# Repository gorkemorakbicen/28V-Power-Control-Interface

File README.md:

# 28 V Power Control Interface

Four-layer PCB design for a nominal 28 V DC input, with input protection, a 5 V buck converter, a 3.3 V logic supply, STM32 voltage-sensing inputs, and a CAN physical interface.

> **Project status:** Schematic capture and PCB layout are complete. The design report records zero KiCad ERC/DRC errors. **No PCB has been fabricated, no firmware is included, and no electrical or EMC measurements have been performed.** All calculated operating values below are design estimates, not test results.

## Overview

This personal hardware-design project explores the process of developing a compact monitoring and communication board for a nominal 28 V DC supply. The work covers component selection, hand calculations, schematic capture, four-layer PCB layout, basic design-rule verification, and technical documentation.

The board is *not* an experimentally validated power supply or a product qualified for automotive, aviation, or industrial transient/EMC standards.

## Key specifications

| Item | Design value / implementation |
| --- | --- |
| Nominal input | 28 V DC |
| Input protection | 1 A fuse, SMBJ36CA bidirectional TVS, P-channel MOSFET reverse-polarity stage, gate Zener |
| Main converter | Texas Instruments LM5164 synchronous buck |
| Buck output | Approximately 5 V; **1 A design target** (not measured) |
| Approximate switching frequency | 303 kHz, calculated from the selected RON resistor |
| Power inductor | 47 µH, Coilcraft MSS1260T-473MLD |
| Logic supply | 3.3 V, TLV75533 LDO |
| Microcontroller | STM32G0B1CBT6, 16 MHz external crystal |
| Voltage-sensing inputs | Resistor-divider/RC-filter networks for nominal 5 V and 28 V rails, connected to STM32 ADC pins |
| CAN interface | NXP TJA1049 transceiver, CAN-line ESD protection, optional 120 Ω termination (DNP) |
| Programming interface | 5-pin SWD header and reset pushbutton |
| PCB size | 70.25 × 67.75 mm |
| PCB stack-up | F.Cu / In1.Cu (GND) / In2.Cu (GND) / B.Cu; nominal 1.6 mm board thickness |
| EDA tool | KiCad 10.0 |

## System architecture

```mermaid
flowchart TD
    A["28 V DC input"] --> B["Fuse, TVS and PMOS protection"]
    B --> C["LM5164 buck: 5 V"]
    C --> D["TLV75533 LDO: 3.3 V"]
    D --> E["STM32G0B1 controller"]
    C --> F["TJA1049 CAN transceiver"]
    E <--> F
    B --> G["28 V sensing divider"]
    C --> H["5 V sensing divider"]
    G --> E
    H --> E
```

The STM32 hardware provides ADC connections for rail monitoring and digital connections to the CAN transceiver. Firmware for sampling, calibration, reporting, and CAN communication remains future work.

## Design highlights

### 1. Input protection

- A 1 A fuse is provided for sustained overcurrent protection.
- An SMBJ36CA TVS is used for transient suppression; its standoff and clamping characteristics must be assessed against a defined source and transient profile.
- A P-channel MOSFET provides reverse-polarity protection. A 12 V Zener network limits the magnitude of its gate-to-source voltage.
- Protection coordination and survival under specified surge waveforms have **not** been verified by test.

### 2. Buck converter and component sizing

- The LM5164 stage converts a nominal 28 V input into an approximately 5 V rail.
- The selected 316 kΩ / 100 kΩ feedback divider gives a nominal calculated output of approximately **4.992 V**.
- The chosen 47 µH inductor and approximately 303 kHz switching frequency yield a calculated inductor-current ripple of **0.288 A** at the nominal design point.
- A 22 µF output capacitor is populated; the second 22 µF position (C7) is marked **DNP**.
- PCB placement emphasizes the switching-current loop, a restrained SW-node area, and feedback routing away from noisy nodes.

### 3. Monitoring, programming, and CAN

- The 5 V measurement divider scales a nominal 5 V input to approximately **2.500 V** at the ADC input.
- The 28 V measurement divider scales a nominal 28 V input to approximately **0.824 V**.
- Both measurement paths include RC filtering. Appropriate ADC sampling time and calibration would need to be addressed in firmware.
- The CAN physical interface uses a TJA1049 transceiver and an ESD suppressor. A 120 Ω termination position (R15) is provided but not populated by default; termination depends on the node's position in the CAN network.

### 4. Four-layer PCB

The two internal copper layers are assigned to GND fills to support return-current paths for top- and bottom-layer routing. Component placement considers the buck power loop, local MCU decoupling, crystal proximity, and CAN protection near the external connector.

See the [four-page PCB layer exports](docs/PCB_Layer_Exports.pdf), a [color top-layer view](docs/PCB_Top_Layer_View.pdf), and the [complete schematic](docs/Complete_Schematic.pdf).

## Verification and limitations

| Activity | Status |
| --- | --- |
| Component selection and hand calculations | Documented |
| Schematic capture and PCB layout | Complete |
| KiCad ERC / DRC | **0 errors recorded in the design report**; not independently rerun for this publication |
| Physical PCB fabrication and assembly | Not performed |
| Power-up, oscilloscope, thermal, and CAN tests | Not performed |
| Embedded firmware and closed-loop control | Not included |
| Defined transient/EMC standard compliance | Not designed or verified |

The layout's passing design-rule checks do not establish electrical performance, manufacturability, or standards compliance. In particular, transient protection, thermal behavior, regulator stability, and sensing accuracy require further review and practical validation.

## Repository contents

```text
28V-Power-Control-Interface/
├── README.md
├── hardware/
│   ├── 28V_Power_Control_Interface.kicad_pro
│   ├── 28V_Power_Control_Interface.kicad_sch
│   ├── MCU_CAN.kicad_sch
│   └── 28V_Power_Control_Interface.kicad_pcb
├── docs/
│   ├── Technical_Design_Report_TR.pdf
│   ├── Complete_Schematic.pdf
│   ├── PCB_Layer_Exports.pdf
│   ├── PCB_Top_Layer_View.pdf
│   └── BOM.xlsx
└── images/
    └── PCB_3D.png
```

### Open the design

1. Install a compatible version of **KiCad 10**.
2. Open `hardware/28V_Power_Control_Interface.kicad_pro`.
3. Keep the top-level schematic and `MCU_CAN.kicad_sch` in the same directory so the hierarchical sheet resolves correctly.

### Documentation

- [Technical design report (Turkish, 18 pages)](docs/Technical_Design_Report_TR.pdf) — design rationale, calculations, electrical assumptions, PCB decisions, and limitations.
- [Complete schematic (PDF)](docs/Complete_Schematic.pdf)
- [PCB layer exports (four-page PDF)](docs/PCB_Layer_Exports.pdf)
- [Color top-layer view (PDF)](docs/PCB_Top_Layer_View.pdf)
- [Bill of materials (Excel)](docs/BOM.xlsx) — includes part numbers and DNP information.

## Author

**Görkem Orakbiçen**  
Electrical and Electronics Engineering, Dokuz Eylül University

This is an independently developed portfolio design. It does not represent a validated or production-released hardware product.

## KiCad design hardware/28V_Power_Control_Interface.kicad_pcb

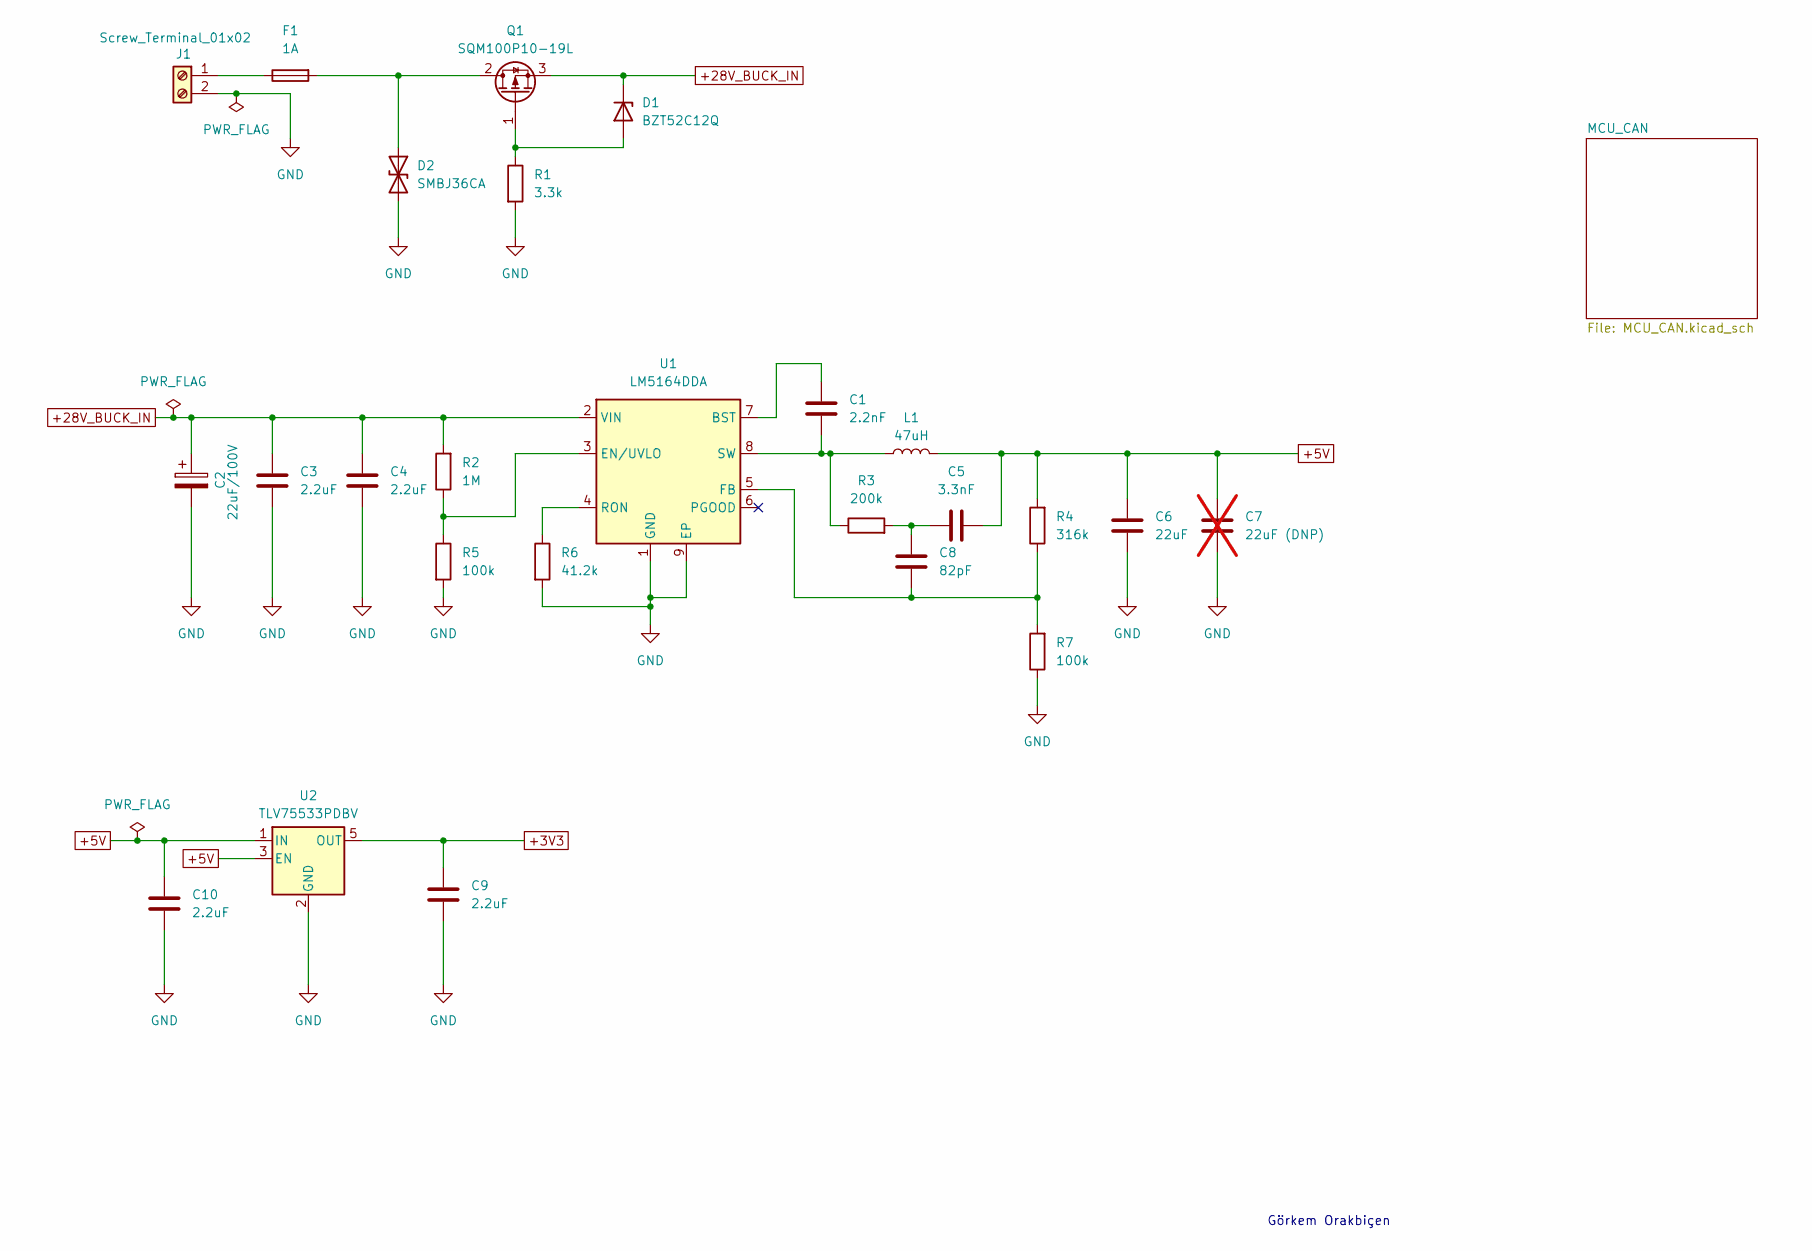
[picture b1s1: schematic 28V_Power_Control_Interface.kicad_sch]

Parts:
C1: 2.2nF; C_0402_1005Metric; MPN GCM155R71H222KA37D
C2: 22uF/100V; CP_Elec_10x10; MPN UCZ2A220MCS1GS
C3, C4: 2.2uF; C_1210_3225Metric; MPN CGA6N3X7R2A225K230AB
C5: 3.3nF; C_0603_1608Metric; MPN GRM188R72A332KA01D
C6: 22uF; C_1210_3225Metric; MPN CGA6P1X7R1C226M250AC
C7: 22uF (DNP); C_1210_3225Metric; MPN CGA6P1X7R1C226M250AC; not fitted
C8: 82pF; C_0603_1608Metric; MPN CGA3E2C0G1H820J080AA
C9, C10: 2.2uF; C_0805_2012Metric; MPN GRM21BR71C225KA12L
D1: BZT52C12Q; D_SOD-123; MPN BZT52C12Q-7-F
D2: SMBJ36CA; D_SMB; MPN SMBJ36CA
F1: 1A; Fuse_Littelfuse-NANO2-451_453; MPN 0451001.MRL
J1: Screw_Terminal_01x02; TerminalBlock_Phoenix_MKDS-1,5-2-5.08_1x02_P5.08mm_Horizont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; MPN 1715721
L1: 47uH; L_Coilcraft_MSS1260-XXX; MPN MSS1260T-473MLD
Q1: SQM100P10-19L; TO-263-3_TabPin2; MPN SQM100P10-19L_GE3
R1: 3.3k; R_1206_3216Metric; MPN AC1206FR-073K3L
R2: 1M; R_0603_1608Metric; MPN AC0603FR-071ML
R3: 200k; R_0603_1608Metric; MPN AC0603FR-07200KL
R4: 316k; R_0603_1608Metric; MPN RT0603BRD07316KL
R5: 100k; R_0603_1608Metric; MPN AC0603FR-07100KL
R6: 41.2k; R_0603_1608Metric; MPN AC0603FR-0741K2L
R7: 100k; R_0603_1608Metric; MPN RT0603BRD07100KL
U1: LM5164DDA; HSOP-8-1EP_3.9x4.9mm_P1.27mm_EP2.41x3.1mm_ThermalVias; MPN LM5164DDAT
U2: TLV75533PDBV; SOT-23-5; MPN TLV75533PDBVR

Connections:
+3V3: C9.1, U2.5 (OUT); also elsewhere on the board
+5V: C5.1, C6.2, C7.2, C10.1, L1.2, R4.2, U2.1 (IN), U2.3 (EN); also elsewhere on the board
+28V_BUCK_IN: C2.1, C3.2, C4.2, D1.1 (K), Q1.3 (S), R2.2, U1.2 (VIN); also elsewhere on the board
GND: C2.2, C3.1, C4.1, C6.1, C7.1, C9.2, C10.2, D2.2 (A2), J1.2, R1.2, R5.2, R6.2, R7.1, U1.1 (GND), U1.9 (EP), U2.2 (GND); also elsewhere on the board
unnamed: C5.2, C8.2, R3.2
unnamed: D1.2 (A), Q1.1 (G), R1.1
unnamed: D2.1 (A1), F1.2, Q1.2 (D)
unnamed: F1.1, J1.1
unnamed: C1.2, U1.7 (BST)
unnamed: R2.1, R5.1, U1.3 (EN/UVLO)
unnamed: C8.1, R4.1, R7.2, U1.5 (FB)
unnamed: R6.1, U1.4 (RON)
unnamed: C1.1, L1.1, R3.1, U1.8 (SW)

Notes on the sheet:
Görkem Orakbiçen

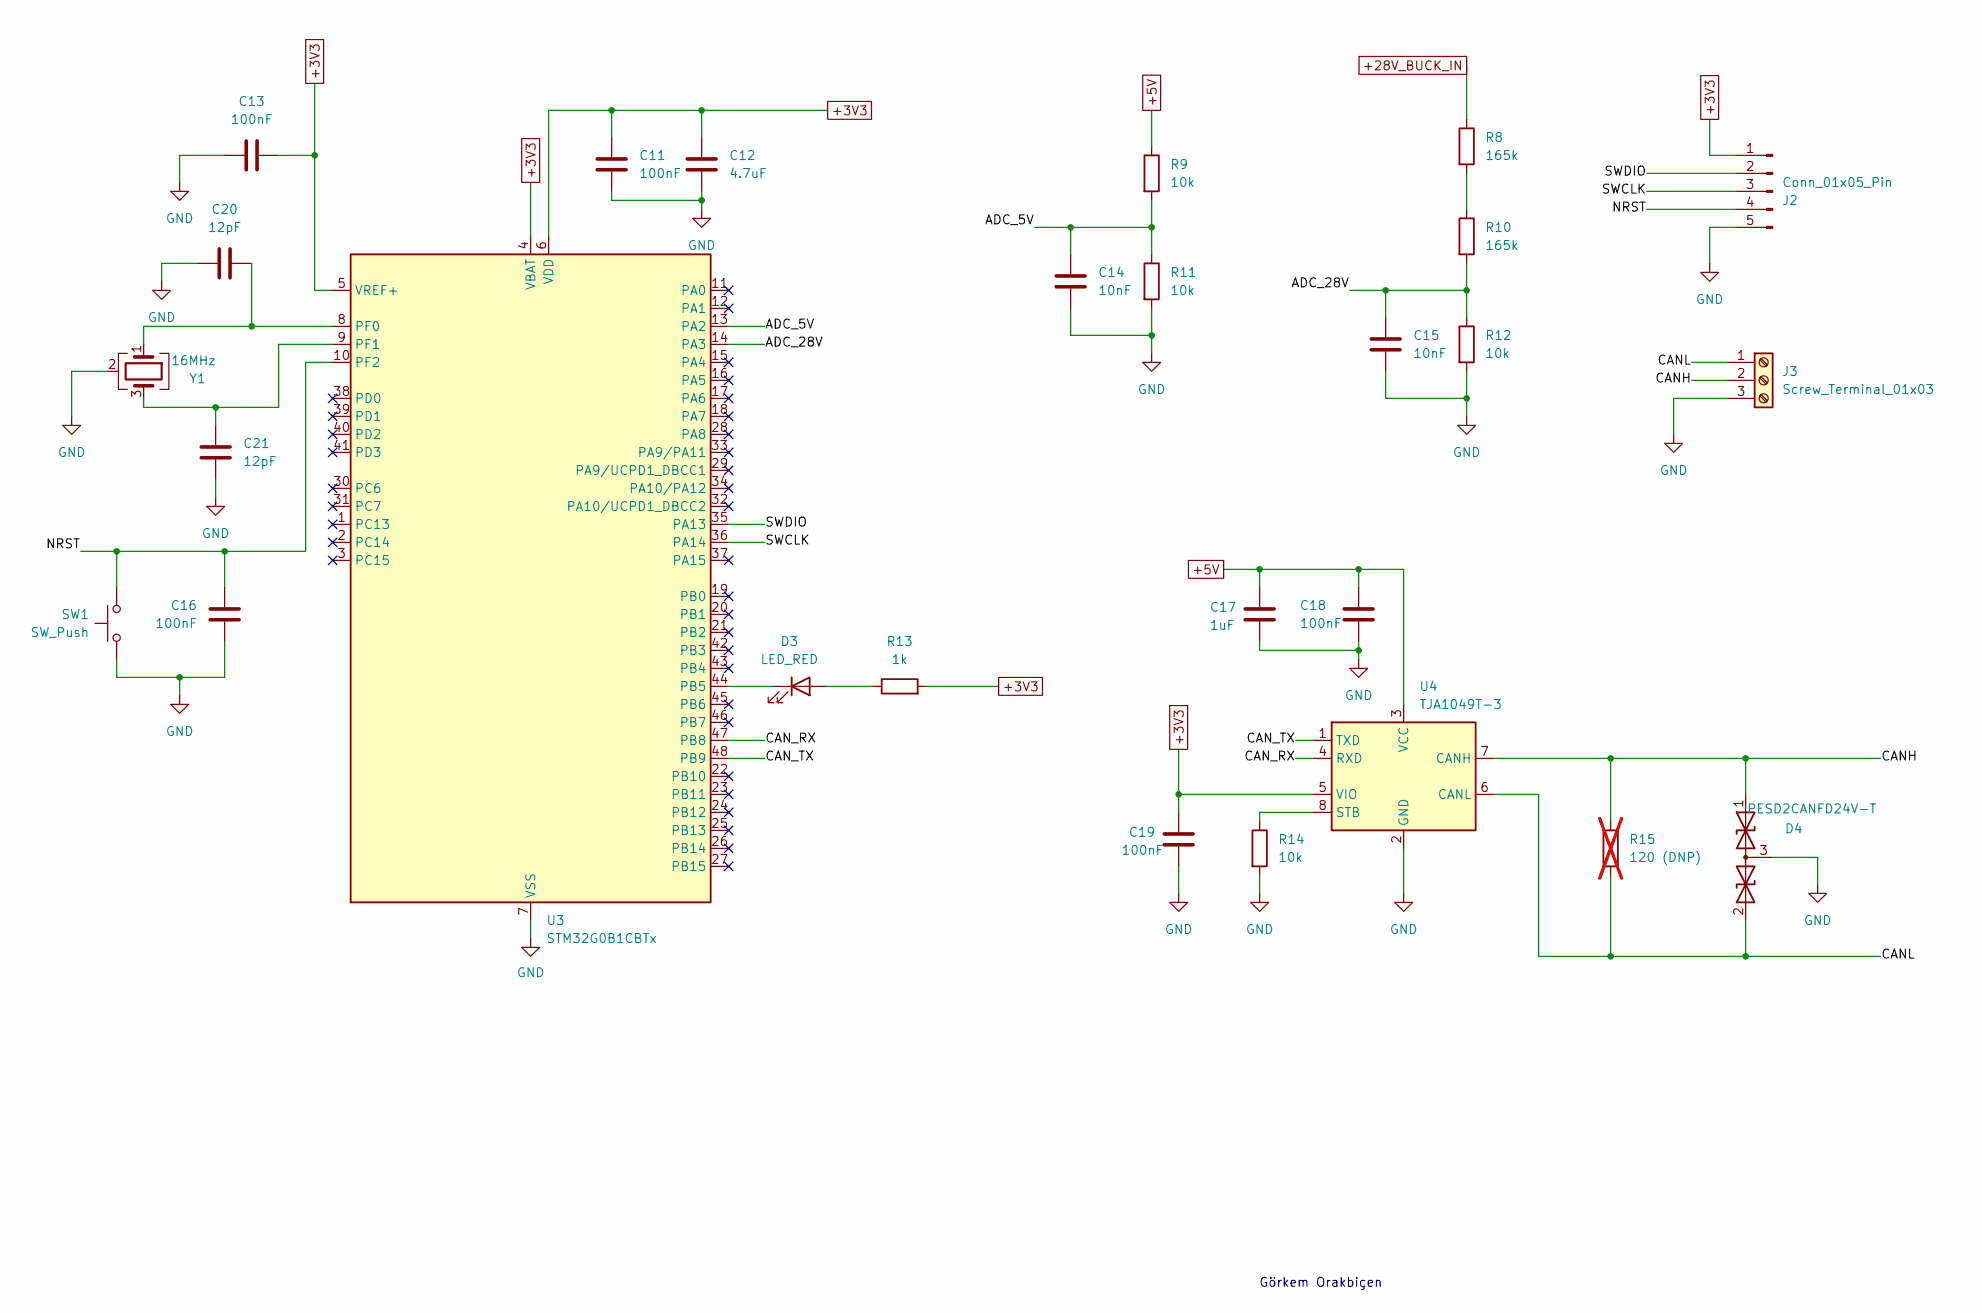
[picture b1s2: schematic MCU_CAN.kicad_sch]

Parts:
C11, C13, C16, C18, C19: 100nF; C_0603_1608Metric; MPN GRM188R72A104KA35D
C12: 4.7uF; C_0805_2012Metric; MPN C2012X7R1C475K125AB
C14, C15: 10nF; C_0603_1608Metric; MPN GRM188R72A103KA01D
C17: 1uF; C_0805_2012Metric; MPN GRM21BR71C105KA01L
C20, C21: 12pF; C_0603_1608Metric; MPN CGA3E2C0G1H120J080AA
D3: LED_RED; LED_0603_1608Metric; MPN LTST-C190KRKT
D4: PESD2CANFD24V-T; SOT-23; MPN PESD2CANFD24V-T
J2: Conn_01x05_Pin; PinHeader_1x05_P2.54mm_Vertical; MPN 61300511121
J3: Screw_Terminal_01x03; TerminalBlock_Phoenix_MKDS-1,5-3-5.08_1x03_P5.08mm_Horizont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; MPN 1715734
R8, R10: 165k; R_0603_1608Metric; MPN AC0603FR-07165KL
R9, R11, R12, R14: 10k; R_0603_1608Metric; MPN AC0603FR-0710KL
R13: 1k; R_0603_1608Metric; MPN AC0603FR-071KL
R15: 120 (DNP); R_1206_3216Metric; MPN AC1206FR-07120RL; not fitted
SW1: SW_Push; SW_SPST_B3U-1000P; MPN B3U-1000P
U3: STM32G0B1CBTx; LQFP-48_7x7mm_P0.5mm; MPN STM32G0B1CBT6
U4: TJA1049T-3; SOIC-8_3.9x4.9mm_P1.27mm; MPN TJA1049T/3/1Z
Y1: 16MHz; Crystal_SMD_3225-4Pin_3.2x2.5mm; MPN CX3225FB16000F0FZZH1

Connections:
+3V3: C11.1, C12.1, C13.2, C19.1, J2.1, R13.2, U3.4 (VBAT), U3.5 (VREF+), U3.6 (VDD), U4.5 (VIO); also elsewhere on the board
+5V: C17.1, C18.1, R9.1, U4.3 (VCC); also elsewhere on the board
+28V_BUCK_IN: R8.1; also elsewhere on the board
/MCU_CAN/ADC_5V: C14.1, R9.2, R11.1, U3.13 (PA2)
/MCU_CAN/ADC_28V: C15.1, R10.2, R12.1, U3.14 (PA3)
/MCU_CAN/CANH: D4.1 (A1), J3.2, R15.1, U4.7 (CANH)
/MCU_CAN/CANL: D4.2 (A2), J3.1, R15.2, U4.6 (CANL)
/MCU_CAN/CAN_RX: U3.47 (PB8), U4.4 (RXD)
/MCU_CAN/CAN_TX: U3.48 (PB9), U4.1 (TXD)
/MCU_CAN/NRST: C16.2, J2.4, SW1.1, U3.10 (PF2)
/MCU_CAN/SWCLK: J2.3, U3.36 (PA14)
/MCU_CAN/SWDIO: J2.2, U3.35 (PA13)
GND: C11.2, C12.2, C13.1, C14.2, C15.2, C16.1, C17.2, C18.2, C19.2, C20.2, C21.2, D4.3 (common), J2.5, J3.3, R11.2, R12.2, R14.2, SW1.2, U3.7 (VSS), U4.2 (GND), Y1.2 (G), Y1.4 (G); also elsewhere on the board
unnamed: D3.2 (A), R13.1
unnamed: D3.1 (K), U3.44 (PB5)
unnamed: R8.2, R10.1
unnamed: C20.1, U3.8 (PF0), Y1.1
unnamed: C21.1, U3.9 (PF1), Y1.3
unnamed: R14.1, U4.8 (STB)

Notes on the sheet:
Görkem Orakbiçen

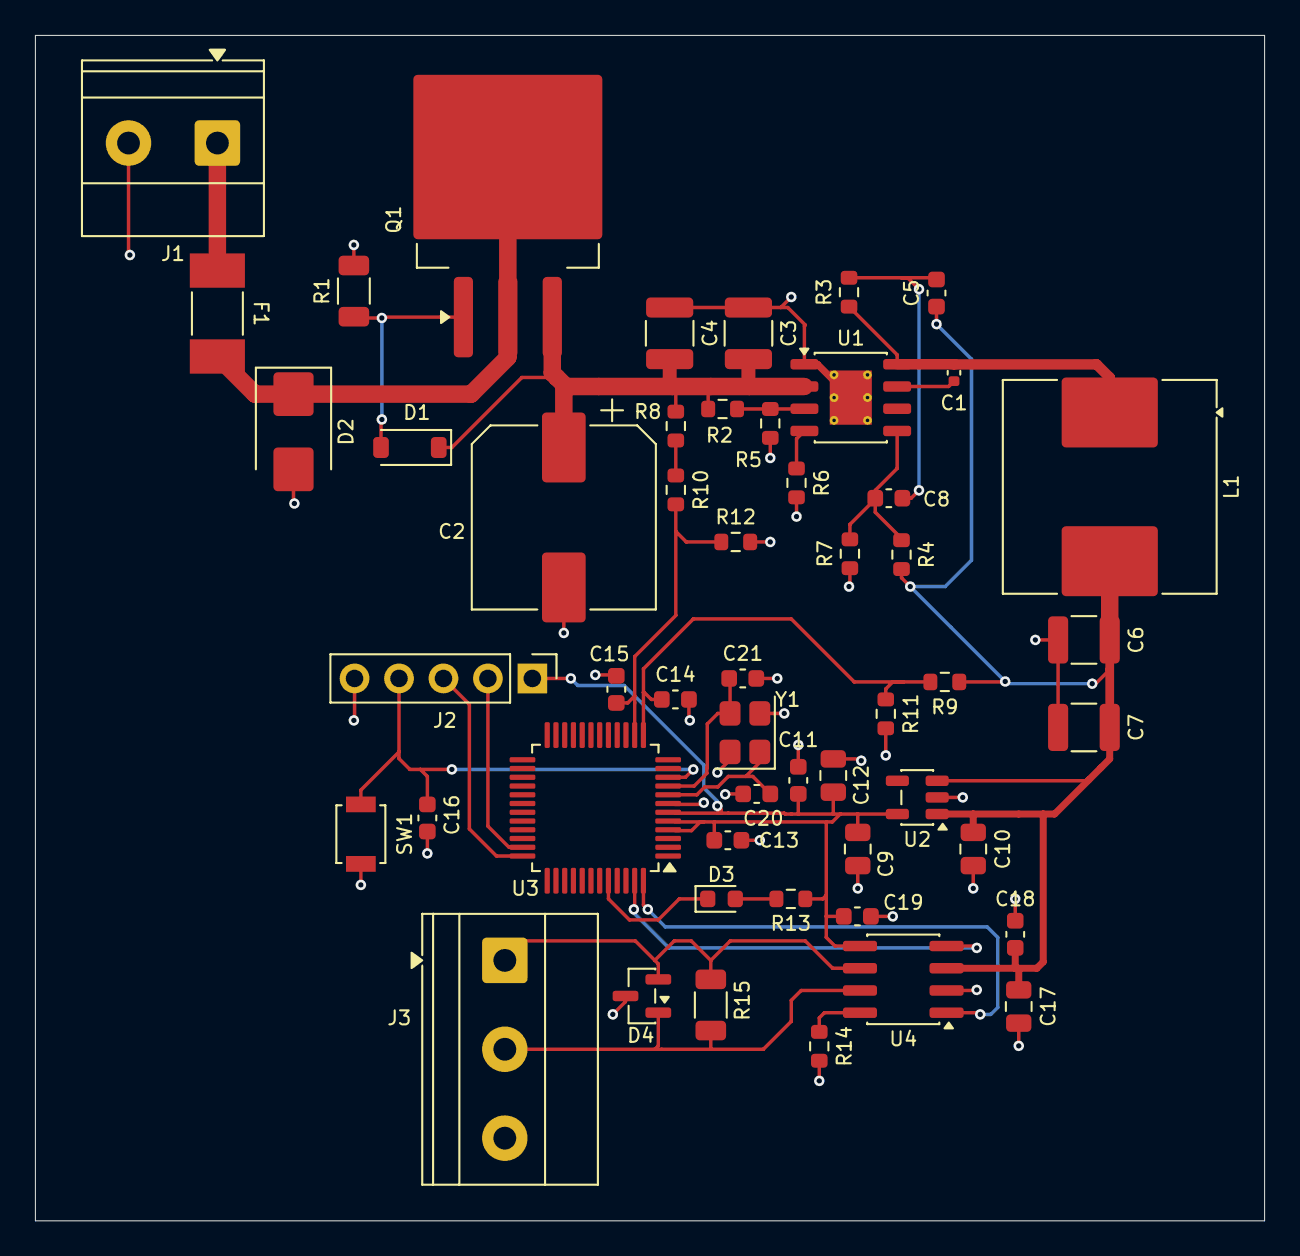
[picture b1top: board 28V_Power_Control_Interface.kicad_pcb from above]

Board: 4 copper layers, 70.2 x 67.8 mm, 52 parts (0 on the bottom side), 28 nets.

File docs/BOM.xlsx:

Referanslar | Adet | Tür | Değer | Üretici | MPN | Footprint | Montaj | Kaynak URL
L1 | 1 | Bobin | 47uH | Coilcraft | MSS1260T-473MLD | Inductor_SMD:L_Coilcraft_MSS1260-XXX | Montaj | https://www.coilcraft.com/en-us/products/power/shielded-indu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
SW1 | 1 | Buton | SW_Push | Omron | B3U-1000P | Button_Switch_SMD:SW_SPST_B3U-1000P | Montaj | https://omronfs.omron.com/en_US/ecb/products/pdf/en-b3u.pdf
R1 | 1 | Direnç | 3.3k | Yageo | AC1206FR-073K3L | Resistor_SMD:R_1206_3216Metric | Montaj | https://yageogroup.com/component-documentation/download/spec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
R13 | 1 | Direnç | 1k | Yageo | AC0603FR-071KL | Resistor_SMD:R_0603_1608Metric | Montaj | https://www.digikey.com/en/products/detail/yageo/AC0603FR-07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
R15 | 1 | Direnç | 120 (DNP) | Yageo | AC1206FR-07120RL | Resistor_SMD:R_1206_3216Metric | DNP | https://www.digikey.com/en/products/detail/yageo/AC1206FR-07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
R2 | 1 | Direnç | 1M | Yageo | AC0603FR-071ML | Resistor_SMD:R_0603_1608Metric | Montaj | https://www.digikey.com/en/products/detail/yageo/AC0603FR-07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
R3 | 1 | Direnç | 200k | Yageo | AC0603FR-07200KL | Resistor_SMD:R_0603_1608Metric | Montaj | https://yageogroup.com/component-documentation/download/spec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
R4 | 1 | Direnç | 316k | Yageo | RT0603BRD07316KL | Resistor_SMD:R_0603_1608Metric | Montaj | https://www.digikey.com/en/products/detail/yageo/RT0603BRD07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
R5 | 1 | Direnç | 100k | Yageo | AC0603FR-07100KL | Resistor_SMD:R_0603_1608Metric | Montaj | https://yageogroup.com/component-documentation/download/spec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
R6 | 1 | Direnç | 41.2k | Yageo | AC0603FR-0741K2L | Resistor_SMD:R_0603_1608Metric | Montaj | https://www.digikey.com/en/products/detail/yageo/AC0603FR-07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
R7 | 1 | Direnç | 100k | Yageo | RT0603BRD07100KL | Resistor_SMD:R_0603_1608Metric | Montaj | https://yageogroup.com/component-documentation/download/spec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
R8, R10 | 2 | Direnç | 165k | Yageo | AC0603FR-07165KL | Resistor_SMD:R_0603_1608Metric | Montaj | https://www.digikey.com/en/products/detail/yageo/AC0603FR-07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
R9, R11, R12, R14 | 4 | Direnç | 10k | Yageo | AC0603FR-0710KL | Resistor_SMD:R_0603_1608Metric | Montaj | https://www.digikey.com/en/products/detail/yageo/AC0603FR-07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
D1 | 1 | Diyot/LED | BZT52C12Q | Diodes Incorporated | BZT52C12Q-7-F | Diode_SMD:D_SOD-123 | Montaj | https://www.digikey.com/en/products/detail/diodes-incorporat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
D2 | 1 | Diyot/LED | SMBJ36CA | Littelfuse | SMBJ36CA | Diode_SMD:D_SMB | Montaj | https://www.littelfuse.com/assetdocs/tvs-diodes-smbj-series-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
D3 | 1 | Diyot/LED | LED_RED | Lite-On | LTST-C190KRKT | LED_SMD:LED_0603_1608Metric | Montaj | https://www.digikey.com/en/products/detail/liteon/LTST-C190K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
D4 | 1 | Diyot/LED | PESD2CANFD24V-T | Nexperia | PESD2CANFD24V-T | Package_TO_SOT_SMD:SOT-23 | Montaj | https://assets.nexperia.com/documents/data-sheet/PESD2CANFD2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
U1 | 1 | Entegre | LM5164DDA | Texas Instruments | LM5164DDAT | Package_SO:HSOP-8-1EP_3.9x4.9mm_P1.27mm_EP2.41x3.1mm_ThermalVias | Montaj | https://www.ti.com/lit/ds/symlink/lm5164.pdf?ts=159831186425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
U2 | 1 | Entegre | TLV75533PDBV | Texas Instruments | TLV75533PDBVR | Package_TO_SOT_SMD:SOT-23-5 | Montaj | http://www.ti.com/lit/ds/symlink/tlv755p.pdf
U3 | 1 | Entegre | STM32G0B1CBTx | STMicroelectronics | STM32G0B1CBT6 | Package_QFP:LQFP-48_7x7mm_P0.5mm | Montaj | https://www.st.com/resource/en/datasheet/stm32g0b1cb.pdf
U4 | 1 | Entegre | TJA1049T-3 | NXP | TJA1049T/3/1Z | Package_SO:SOIC-8_3.9x4.9mm_P1.27mm | Montaj | http://www.nxp.com/docs/en/data-sheet/TJA1049.pdf
C1 | 1 | Kondansatör | 2.2nF | Murata | GCM155R71H222KA37D | Capacitor_SMD:C_0402_1005Metric | Montaj | https://www.digikey.com/en/products/detail/murata-electronic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
C11, C13, C16, C18, C19 | 5 | Kondansatör | 100nF | Murata | GRM188R72A104KA35D | Capacitor_SMD:C_0603_1608Metric | Montaj | https://www.digikey.com/en/products/detail/murata-electronic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
C12 | 1 | Kondansatör | 4.7uF | TDK | C2012X7R1C475K125AB | Capacitor_SMD:C_0805_2012Metric | Montaj | https://www.digikey.lv/en/products/detail/tdk/C2012X7R1C475K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
C14, C15 | 2 | Kondansatör | 10nF | Murata | GRM188R72A103KA01D | Capacitor_SMD:C_0603_1608Metric | Montaj | https://www.digikey.com/en/products/detail/murata-electronic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
C17 | 1 | Kondansatör | 1uF | Murata | GRM21BR71C105KA01L | Capacitor_SMD:C_0805_2012Metric | Montaj | https://www.digikey.com/en/products/detail/murata-electronic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
C2 | 1 | Kondansatör | 22uF/100V | Nichicon | UCZ2A220MCS1GS | Capacitor_SMD:CP_Elec_10x10 | Montaj | https://www.nichicon.com/en-us/part/ucz2a220mcs1gs/3000/
C20, C21 | 2 | Kondansatör | 12pF | TDK | CGA3E2C0G1H120J080AA | Capacitor_SMD:C_0603_1608Metric | Montaj | https://product.tdk.com/system/files/dam/doc/product/capacit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
C3, C4 | 2 | Kondansatör | 2.2uF | TDK | CGA6N3X7R2A225K230AB | Capacitor_SMD:C_1210_3225Metric | Montaj | https://product.tdk.com/en/search/capacitor/ceramic/mlcc/inf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
C5 | 1 | Kondansatör | 3.3nF | Murata | GRM188R72A332KA01D | Capacitor_SMD:C_0603_1608Metric | Montaj | https://www.digikey.com/en/products/detail/murata-electronic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
C6 | 1 | Kondansatör | 22uF | TDK | CGA6P1X7R1C226M250AC | Capacitor_SMD:C_1210_3225Metric | Montaj | https://product.tdk.com/en/search/capacitor/ceramic/mlcc/inf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
C7 | 1 | Kondansatör | 22uF (DNP) | TDK | CGA6P1X7R1C226M250AC | Capacitor_SMD:C_1210_3225Metric | DNP | https://product.tdk.com/en/search/capacitor/ceramic/mlcc/inf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
C8 | 1 | Kondansatör | 82pF | TDK | CGA3E2C0G1H820J080AA | Capacitor_SMD:C_0603_1608Metric | Montaj | https://product.tdk.com/en/search/capacitor/ceramic/mlcc/inf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
C9, C10 | 2 | Kondansatör | 2.2uF | Murata | GRM21BR71C225KA12L | Capacitor_SMD:C_0805_2012Metric | Montaj | https://www.digikey.com/en/products/detail/murata-electronic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
J1 | 1 | Konnektör | Screw_Terminal_01x02 | Phoenix Contact | 1715721 | TerminalBlock_Phoenix:TerminalBlock_Phoenix_MKDS-1,5-2-5.08_1x02_P5.08mm_Horizo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 | Montaj | https://www.phoenixcontact.com/tr-tr/urunler/baskili-devre-l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
J2 | 1 | Konnektör | Conn_01x05_Pin | Würth Elektronik | 61300511121 | Connector_PinHeader_2.54mm:PinHeader_1x05_P2.54mm_Vertical | Montaj | https://www.digikey.com/en/products/detail/w%C3%BCrth-elektr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
J3 | 1 | Konnektör | Screw_Terminal_01x03 | Phoenix Contact | 1715734 | TerminalBlock_Phoenix:TerminalBlock_Phoenix_MKDS-1,5-3-5.08_1x03_P5.08mm_Horizo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 | Montaj | https://www.phoenixcontact.com/tr-tr/urunler/baskili-devre-l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
Y1 | 1 | Kristal | 16MHz | Kyocera | CX3225FB16000F0FZZH1 | Crystal:Crystal_SMD_3225-4Pin_3.2x2.5mm | Montaj | https://ele.kyocera.com/assets/products/crystal-device/speci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
Q1 | 1 | MOSFET | SQM100P10-19L | Vishay | SQM100P10-19L_GE3 | Package_TO_SOT_SMD:TO-263-3_TabPin2 | Montaj | https://www.vishay.com/docs/75583/sqm100p10-19l.pdf
F1 | 1 | Sigorta | 1A | Littelfuse | 0451001.MRL | Fuse:Fuse_Littelfuse-NANO2-451_453 | Montaj | https://www.littelfuse.com/assetdocs/fuse-451-and-453-datash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
